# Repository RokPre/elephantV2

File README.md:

# About
This keyboard is a split fully wireless ergonomic keyboard. Its layout is 3 rows and 6 columns with a 4 key thumb cluster. Is it designed to use choc switches, for a lower profile. It also includes a 3d case for carrying it around.

# Parts list
| Part | Name | Quantity | Link |
| --- | --- | --- | --- |
| Microcontroller | nRF52840 | 2 | [link](https://www.aliexpress.com/item/1005007040333351.html)|
| Switches |    | 56 | |
| Battery | | 2| |
| Diodes| | 56 | |
| Heat inserts and screws| | 10 | |
| Feet | | 8 | |

# PCB
The pcb should be reversable. T

# Case
The case is designed out of two parts, the top half and the bottom half. The top half goes between the switches and the pcb, it also goes over the edge of the pcb, hangs over it. The bottom of the case is super slim and shows the hotswap sockets, like TOTEM.
There are two head inserts, for a m3 screw that hold together the top and the bttom of the case.

# To-do
- [x] Reversable hotswap sockets
- [ ] Add footprints for pcb parts
	- [ ] Choc key switches
	- [ ] Diodes
	- [ ] nRF microcontroller
  - [ ] Battery
- [ ] Add 3d models for parts
	- [ ] Choc key switches
	- [ ] Diodes
	- [ ] NRF microcontroller
  - [ ] Battery
- [ ] 3d case
  - [ ] tenting
- [ ] Carry vase
- [ ] ZMK configuration

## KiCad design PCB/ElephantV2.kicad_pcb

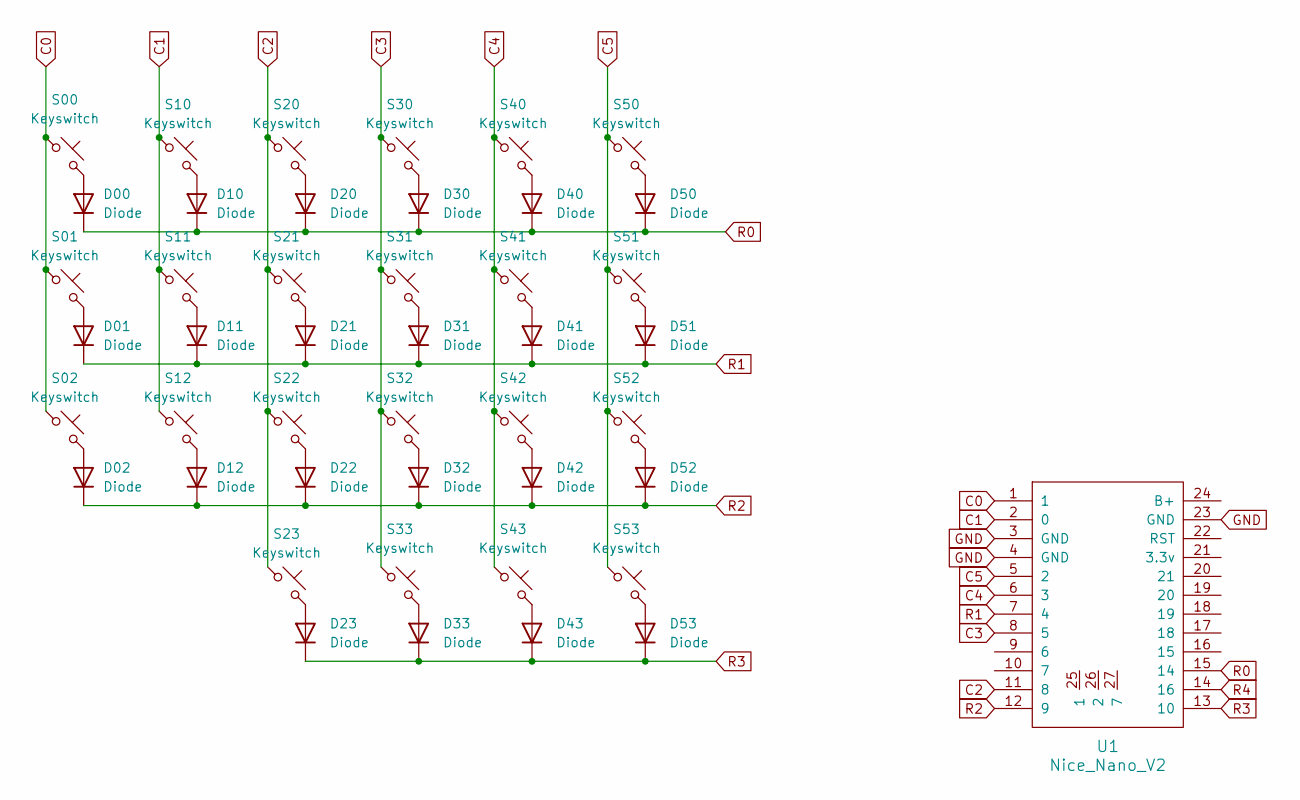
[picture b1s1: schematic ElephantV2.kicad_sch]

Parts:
D00, D01, D02, D10, D11, D12, D20, D21, D22, D23, D30, D31, D32, D33, D40, D41, D42, D43, D50, D51, D52, D53: Diode; Diode_SOD-123
S00, S01, S02, S10, S11, S12, S20, S21, S22, S23, S30, S31, S32, S33, S40, S41, S42, S43, S50, S51, S52, S53: Keyswitch; Choc_1.00u_reversable
U1: Nice_Nano_V2; Arduino_Pro_Micro

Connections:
C0: S00.1, S01.1, S02.1, U1.1
C1: S10.1, S11.1, S12.1, U1.2 (0)
C2: S20.1, S21.1, S22.1, S23.1, U1.11 (8)
C3: S30.1, S31.1, S32.1, S33.1, U1.8 (5)
C4: S40.1, S41.1, S42.1, S43.1, U1.6 (3)
C5: S50.1, S51.1, S52.1, S53.1, U1.5 (2)
GND: U1.3 (GND), U1.4 (GND), U1.23 (GND)
unnamed: D00.2 (A), S00.2
unnamed: D01.2 (A), S01.2
unnamed: D02.2 (A), S02.2
unnamed: D10.2 (A), S10.2
unnamed: D11.2 (A), S11.2
unnamed: D12.2 (A), S12.2
unnamed: D20.2 (A), S20.2
unnamed: D21.2 (A), S21.2
unnamed: D22.2 (A), S22.2
unnamed: D23.2 (A), S23.2
unnamed: D30.2 (A), S30.2
unnamed: D31.2 (A), S31.2
unnamed: D32.2 (A), S32.2
unnamed: D33.2 (A), S33.2
unnamed: D40.2 (A), S40.2
unnamed: D41.2 (A), S41.2
unnamed: D42.2 (A), S42.2
unnamed: D43.2 (A), S43.2
unnamed: D50.2 (A), S50.2
unnamed: D51.2 (A), S51.2
unnamed: D52.2 (A), S52.2
unnamed: D53.2 (A), S53.2
R0: D00.1 (K), D10.1 (K), D20.1 (K), D30.1 (K), D40.1 (K), D50.1 (K), U1.15 (14)
R1: D01.1 (K), D11.1 (K), D21.1 (K), D31.1 (K), D41.1 (K), D51.1 (K), U1.7 (4)
R2: D02.1 (K), D12.1 (K), D22.1 (K), D32.1 (K), D42.1 (K), D52.1 (K), U1.12 (9)
R3: D23.1 (K), D33.1 (K), D43.1 (K), D53.1 (K), U1.13 (10)
R4: U1.14 (16)

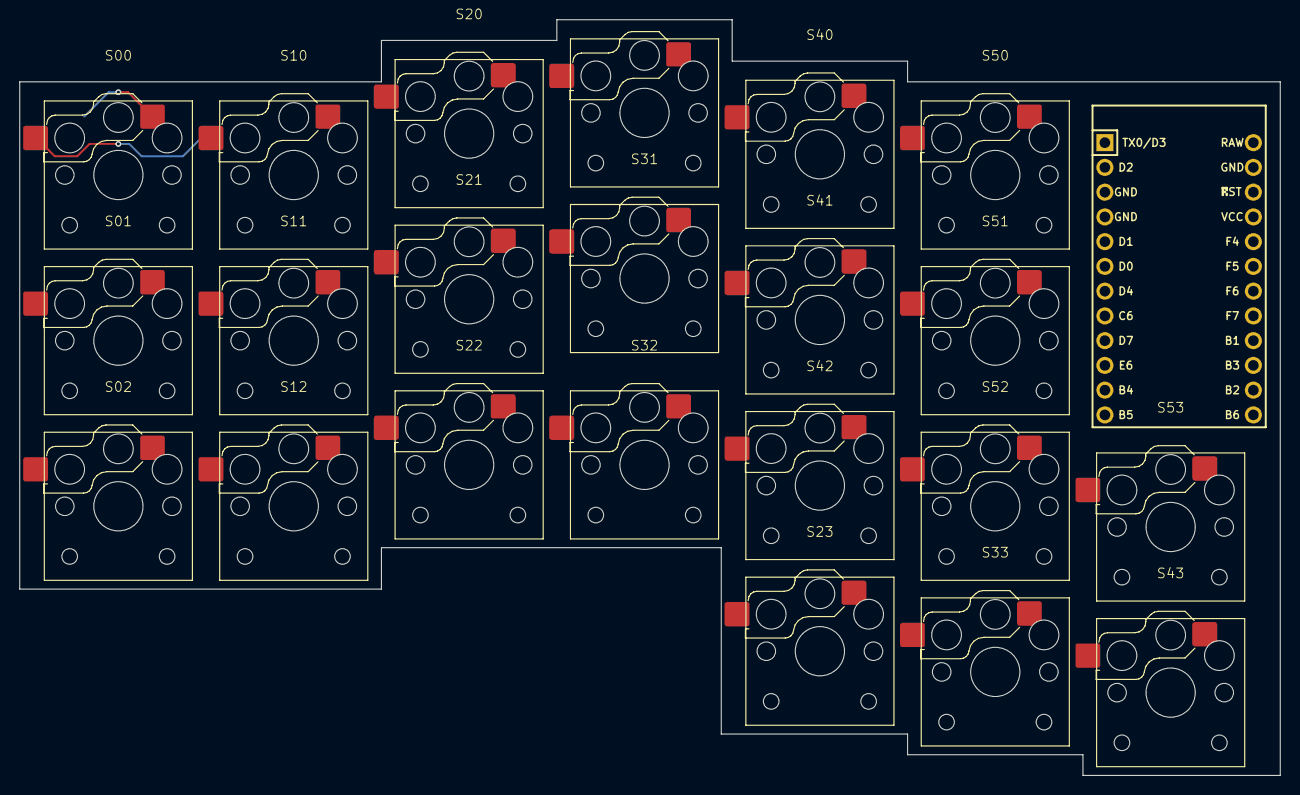
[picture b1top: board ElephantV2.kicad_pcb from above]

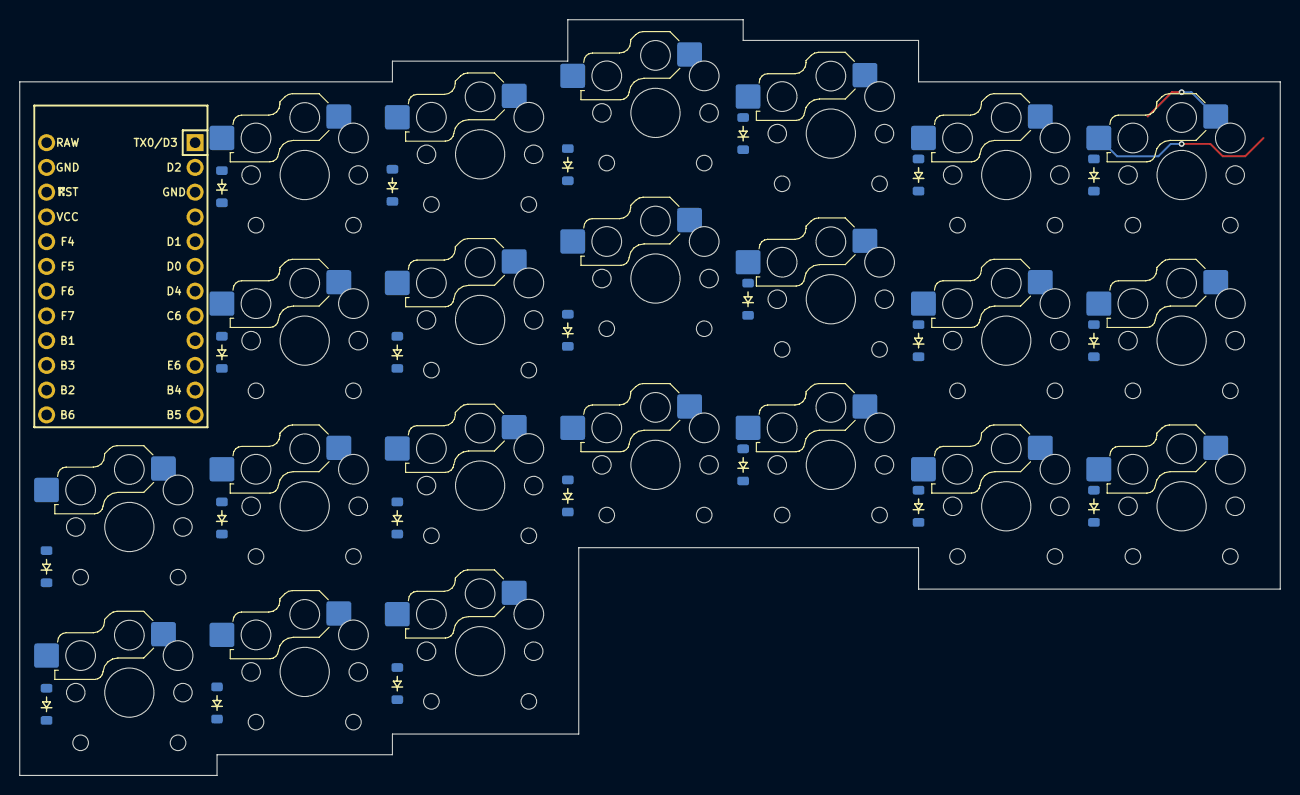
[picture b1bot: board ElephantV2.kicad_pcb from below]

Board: 2 copper layers, 129.4 x 77.6 mm, 45 parts (22 on the bottom side), 33 nets.

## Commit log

2024-12-03 add readme
2024-12-18 Improved the layout of the keyboard in the schematic and pcb. Updated the readmefile
2025-01-15 Made it choc changed the layout to be 3x6_4
2025-01-15 Made the top shield
